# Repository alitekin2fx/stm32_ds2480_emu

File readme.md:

# STM32 DS2480 emulation project.
DS2480 is a 1-Wire line driver IC that works with OneWireLinkLayer library and several evaluation kit softwares from Maxim. In this project i have demostrated how to emulate DS2480 chip on STM32. You can use this usb stick to access your 1-Wire IC's with above softwares or with your own software using the OneWireLinkLayer library.

# How to upload firmware
1) Download and install the DfuSe application from ST.
2) Solder "DFU" jumper and plug it into USB port.
3) Install driver if needed.
4) Run DfuSe and press "choose" button under "Update and verify action" section.
5) Locate to *.dfu file (software/stm32_ds2480_emu.dfu)
5) Press "Upgrade" button
6) Press "Leave DFU mode" button.
8) Remove solder from "DFU" jumper

# Licenses
- Software license: MIT
- Hardware license: CERN v1.2

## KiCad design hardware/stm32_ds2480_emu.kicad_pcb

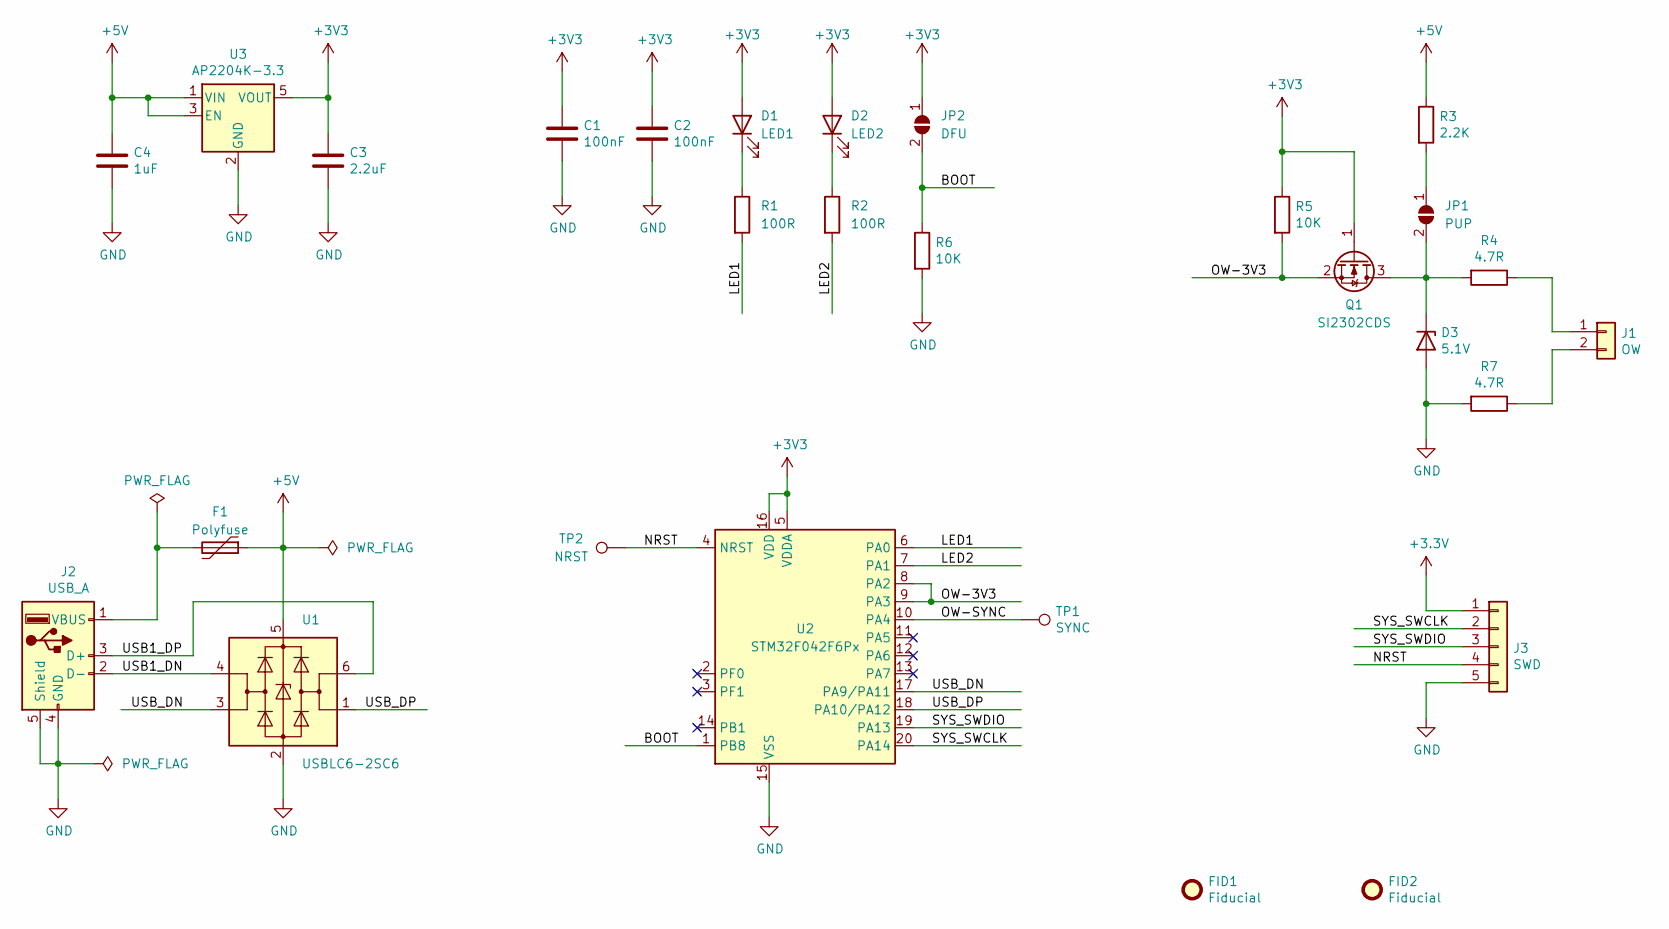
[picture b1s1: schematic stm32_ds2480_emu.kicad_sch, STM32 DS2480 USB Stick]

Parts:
C1, C2: 100nF; C_0603_1608Metric; Part Number CL10B104KB8NNNC
C3: 2.2uF; C_0603_1608Metric; Part Number CL10A225KO8NNNC
C4: 1uF; C_0603_1608Metric; Part Number CL10A105KO8NNNC
D1: LED1; LED_0603_1608Metric; Part Number LTST-C190KGKT
D2: LED2; LED_0603_1608Metric; Part Number LTST-C191KRKT
D3: 5.1V; D_SOT-23_ANK; Part Number BZX84C5V1-HT
F1: Polyfuse; Fuse_0805_2012Metric; Part Number MF-PSMF010X-2
FID1, FID2: Fiducial; Fiducial_0.5mm_Mask1.5mm
J1: OW; PinHeader_1x02_P2.54mm_Vertical
J2: USB_A; USB_A_CNCTech_1001-011-01101_Horizontal; Part Number DS1098-WN0
J3: SWD; PinHeader_1x05_P1.27mm_Vertical
JP1: PUP; SolderJumper-2_P1.3mm_Open_RoundedPad1.0x1.5mm
JP2: DFU; SolderJumper-2_P1.3mm_Open_RoundedPad1.0x1.5mm
Q1: SI2302CDS; SOT-23; Part Number SI2302CDS-T1-GE3
R1, R2: 100R; R_0603_1608Metric; Part Number 0603SAJ0101T5E
R3: 2.2K; R_0805_2012Metric; Part Number 0805S8J0222T5E
R4, R7: 4.7R; R_0805_2012Metric; Part Number 0805S8J047JT5E
R5, R6: 10K; R_0603_1608Metric; Part Number 0603SAJ0103T5E
TP1: SYNC; TestPoint_Pad_D1.0mm
TP2: NRST; TestPoint_Pad_D1.0mm
U1: USBLC6-2SC6; SOT-23-6; Part Number USBLC6-2SC6
U2: STM32F042F6Px; TSSOP-20_4.4x6.5mm_P0.65mm; Part Number STM32F042F6P6
U3: AP2204K-3.3; SOT-23-5; Part Number AP2204K-3.3TRG1

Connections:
+5V: C4.1, F1.1, R3.1, U1.5 (VBUS), U3.1 (VIN), U3.3 (EN)
/BOOT: JP2.2 (B), R6.1, U2.1 (PB8)
/LED1: R1.2, U2.6 (PA0)
/LED2: R2.2, U2.7 (PA1)
/NRST: J3.4, TP2.1, U2.4 (NRST)
/OW-3V3: Q1.2 (S), R5.2, U2.8 (PA2), U2.9 (PA3)
/OW-SYNC: TP1.1, U2.10 (PA4)
/SYS_SWCLK: J3.2, U2.20 (PA14)
/SYS_SWDIO: J3.3, U2.19 (PA13)
/USB1_DN: J2.2 (D-), U1.4 (I/O2)
/USB1_DP: J2.3 (D+), U1.6 (I/O1)
/USB_DN: U1.3 (I/O2), U2.17 (PA9/PA11)
/USB_DP: U1.1 (I/O1), U2.18 (PA10/PA12)
GND: C1.2, C2.2, C3.2, C4.2, D3.2 (A), J2.4 (GND), J2.5 (Shield), J3.5, R6.2, R7.2, U1.2 (GND), U2.15 (VSS), U3.2 (GND)
unnamed: D1.1 (K), R1.1
unnamed: D2.1 (K), R2.1
unnamed: D3.1 (K), JP1.2 (B), Q1.3 (D), R4.2
unnamed: F1.2, J2.1 (VBUS)
unnamed: J1.1, R4.1
unnamed: J1.2, R7.1
unnamed: JP1.1 (A), R3.2

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
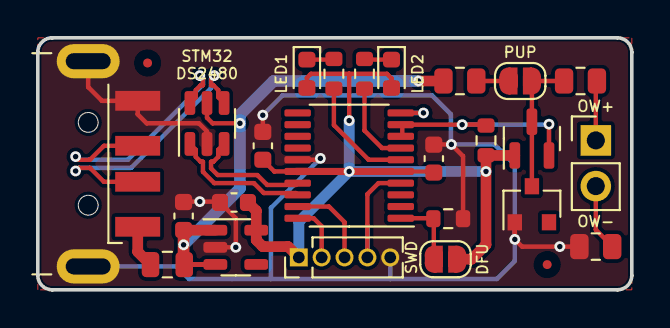
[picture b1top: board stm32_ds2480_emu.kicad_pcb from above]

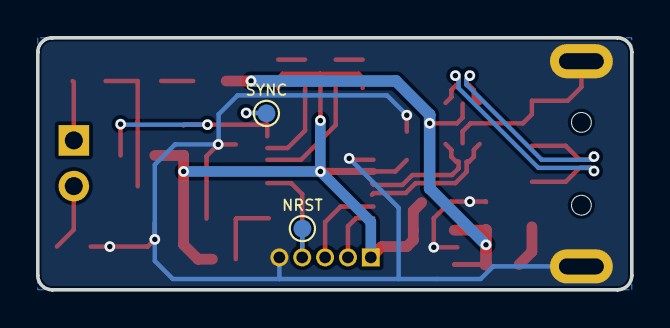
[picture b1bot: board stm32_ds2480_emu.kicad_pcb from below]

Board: 2 copper layers, 33.0 x 14.0 mm, 28 parts (2 on the bottom side), 22 nets.

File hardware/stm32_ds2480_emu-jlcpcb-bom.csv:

Comment,Designator,Footprint,LCSC Part #
"100nF","C1,C2","Capacitor_SMD:C_0603_1608Metric",""
"2.2uF","C3","Capacitor_SMD:C_0603_1608Metric",""
"1uF","C4","Capacitor_SMD:C_0603_1608Metric",""
"LED1","D1","LED_SMD:LED_0603_1608Metric",""
"LED2","D2","LED_SMD:LED_0603_1608Metric",""
"5.1V","D3","Diode_SMD:D_SOT-23_ANK",""
"Polyfuse","F1","Fuse:Fuse_0805_2012Metric",""
"Fiducial","FID1,FID2","Fiducial:Fiducial_0.5mm_Mask1.5mm",""
"OW","J1","Connector_PinHeader_2.54mm:PinHeader_1x02_P2.54mm_Vertical",""
"USB_A","J2","Connector_USB:USB_A_CNCTech_1001-011-01101_Horizontal",""
"SWD","J3","Connector_PinHeader_1.27mm:PinHeader_1x05_P1.27mm_Vertical",""
"PUP","JP1","Jumper:SolderJumper-2_P1.3mm_Open_RoundedPad1.0x1.5mm",""
"DFU","JP2","Jumper:SolderJumper-2_P1.3mm_Open_RoundedPad1.0x1.5mm",""
"SI2302CDS","Q1","Package_TO_SOT_SMD:SOT-23",""
"100R","R1,R2","Resistor_SMD:R_0603_1608Metric",""
"2.2K","R3","Resistor_SMD:R_0805_2012Metric",""
"4.7R","R4,R7","Resistor_SMD:R_0805_2012Metric",""
"10K","R5,R6","Resistor_SMD:R_0603_1608Metric",""
"SYNC","TP1","TestPoint:TestPoint_Pad_D1.0mm",""
"NRST","TP2","TestPoint:TestPoint_Pad_D1.0mm",""
"USBLC6-2SC6","U1","Package_TO_SOT_SMD:SOT-23-6",""
"STM32F042F6Px","U2","Package_SO:TSSOP-20_4.4x6.5mm_P0.65mm",""
"AP2204K-3.3","U3","Package_TO_SOT_SMD:SOT-23-5",""

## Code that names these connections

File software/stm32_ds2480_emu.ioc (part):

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Mcu.Name=STM32F042F6Px
Mcu.Package=TSSOP20
Mcu.UserName=STM32F042F6Px
PA0.GPIOParameters=PinState,GPIO_Label,GPIO_ModeDefaultOutputPP
PA0.GPIO_Label=LED1
PA0.GPIO_ModeDefaultOutputPP=GPIO_MODE_OUTPUT_OD
PA0.PinState=GPIO_PIN_SET
PA0.Signal=GPIO_Output
PA1.GPIOParameters=PinState,GPIO_Label,GPIO_ModeDefaultOutputPP
PA1.GPIO_Label=LED2
PA1.GPIO_ModeDefaultOutputPP=GPIO_MODE_OUTPUT_OD
PA1.PinState=GPIO_PIN_SET
PA1.Signal=GPIO_Output
PA11.Mode=Device
PA11.Signal=USB_DM
PA12.Mode=Device
PA12.Signal=USB_DP
PA13.Mode=Serial_Wire
PA13.Signal=SYS_SWDIO
PA14.Mode=Serial_Wire
PA14.Signal=SYS_SWCLK
PA2.GPIOParameters=GPIO_ModeDefaultPP,GPIO_Label
PA2.GPIO_Label=OW-TX
PA2.GPIO_ModeDefaultPP=GPIO_MODE_AF_OD
PA2.Mode=Asynchronous
PA2.Signal=USART2_TX
PA3.GPIOParameters=GPIO_Label
PA3.GPIO_Label=OW-RX
PA3.Mode=Asynchronous
PA3.Signal=USART2_RX
PA4.GPIOParameters=GPIO_Label
PA4.GPIO_Label=OW-SYNC
PA4.Signal=GPIO_Output
RCC.SYSCLKFreq_VALUE=48000000
RCC.SYSCLKSource=RCC_SYSCLKSOURCE_HSI48
board=custom

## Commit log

2019-05-12 Firmware added
2019-05-14 CDC receive method changes
2019-05-18 DFU file added
2019-05-30 Uart changed to one bit sample mode
2019-08-03 Upgraded to CubeMx 5.2.1
2019-08-31 All componenets moved to top side
2019-09-01 Create LICENSE
2019-09-12 DMA receive error fixed
2020-02-07 New USB stick PCB design
2020-02-07 Search algorithm fixed
2020-02-13 A potential bug is fixed
2021-05-26 Started using KiKit for the panelization.
2021-08-26 Error interrupts are disabled because of incomplete data transfer
